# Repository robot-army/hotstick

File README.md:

# hotstick
An open-source hardware soldering station

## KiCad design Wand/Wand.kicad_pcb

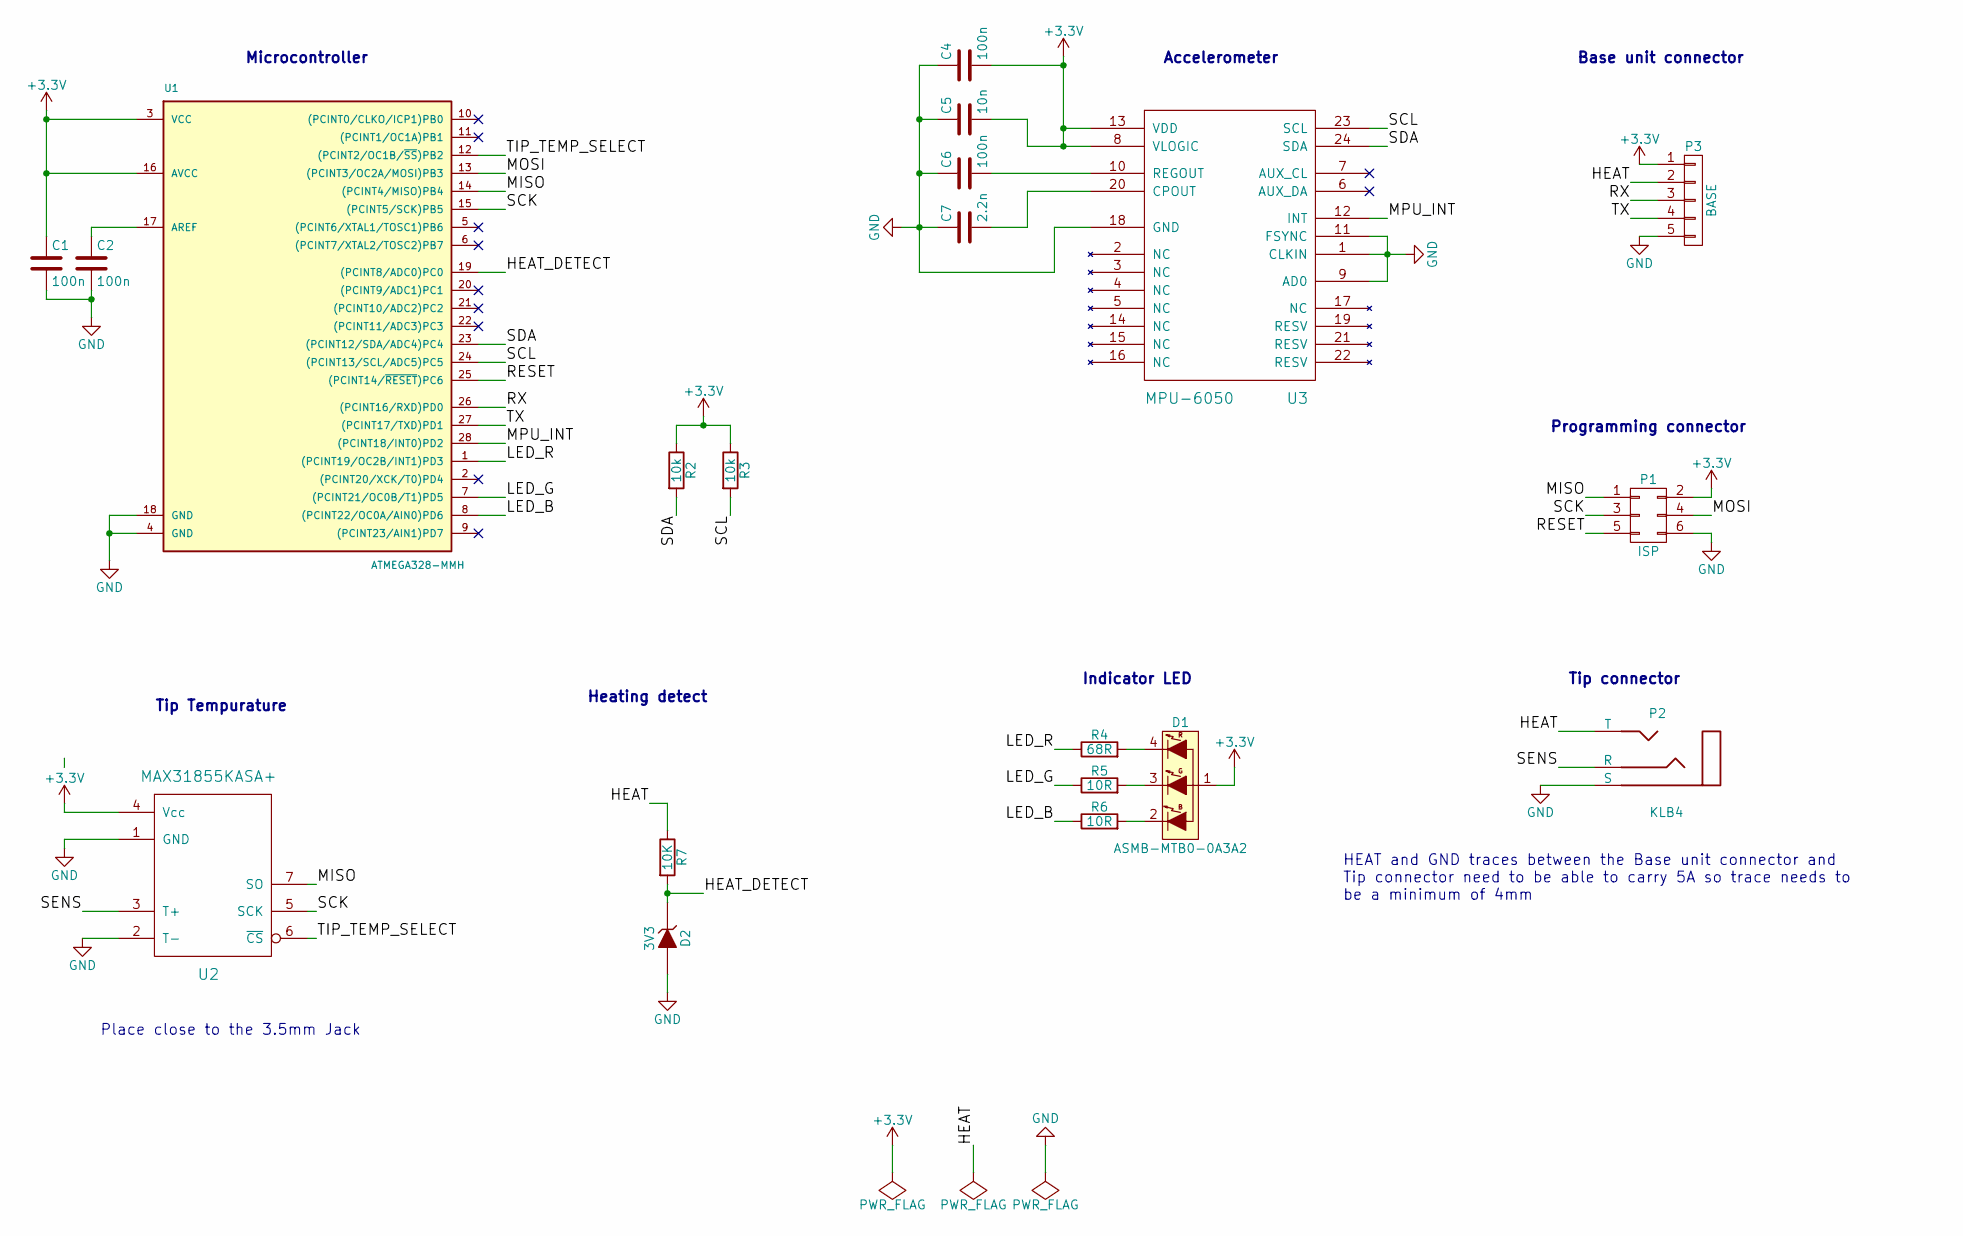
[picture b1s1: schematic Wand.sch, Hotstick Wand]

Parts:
C1, C2, C4, C6: 100n; C_0402
C5: 10n; C_0402
C7: 2.2n; C_0402
D1: ASMB-MTB0-0A3A2; Tri-Colour_LED
D2: 3V3; SOD-523
P1: ISP; ISP_pads_2x3
P2: KLB4; Jack_3.5mm_KLB
P3: BASE; Base_Connector
R2, R3: 10k; R_0402
R4: 68R; R_0402
R5, R6: 10R; R_0402
R7: 10K; R_0402
U1: ATMEGA328-MMH; QFN-28-1EP_4x4mm_Pitch0.45mm
U2: MAX31855KASA+; SOIC-8_3.9x4.9mm_Pitch1.27mm
U3: MPU-6050

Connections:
+3V3: C1.1, C4.2, C5.2, D1.1, P1.2, P3.1, R2.1, R3.1, U1.3 (VCC), U1.16 (AVCC), U2.4 (Vcc), U3.8 (VLOGIC), U3.13 (VDD)
/HEAT: P2.T, P3.2, R7.1
/HEAT_DETECT: D2.1 (K), R7.2, U1.19 ((PCINT8/ADC0)PC0)
/LED_B: R6.1, U1.8 ((PCINT22/OC0A/AIN0)PD6)
/LED_G: R5.1, U1.7 ((PCINT21/OC0B/T1)PD5)
/LED_R: R4.1, U1.1 ((PCINT19/OC2B/INT1)PD3)
/MISO: P1.1, U1.14 ((PCINT4/MISO)PB4), U2.7 (SO)
/MOSI: P1.4, U1.13 ((PCINT3/OC2A/MOSI)PB3)
/MPU_INT: U1.28 ((PCINT18/INT0)PD2), U3.12 (INT)
/RESET: P1.5, U1.25 ((PCINT14/~RESET~)PC6)
/RX: P3.3, U1.26 ((PCINT16/RXD)PD0)
/SCK: P1.3, U1.15 ((PCINT5/SCK)PB5), U2.5 (SCK)
/SCL: R3.2, U1.24 ((PCINT13/SCL/ADC5)PC5), U3.23 (SCL)
/SDA: R2.2, U1.23 ((PCINT12/SDA/ADC4)PC4), U3.24 (SDA)
/SENS: P2.R, U2.3 (T+)
/TIP_TEMP_SELECT: U1.12 ((PCINT2/OC1B/~SS~)PB2), U2.6 (~CS)
/TX: P3.4, U1.27 ((PCINT17/TXD)PD1)
GND: C1.2, C2.2, C4.1, C5.1, C6.1, C7.1, D2.2 (A), P1.6, P2.S, P3.5, U1.4 (GND), U1.18 (GND), U2.1 (GND), U2.2 (T-), U3.1 (CLKIN), U3.9 (AD0), U3.11 (FSYNC), U3.18 (GND)
unnamed: C2.1, U1.17 (AREF)
unnamed: C6.2, U3.10 (REGOUT)
unnamed: C7.2, U3.20 (CPOUT)
unnamed: D1.2 (B), R6.2
unnamed: D1.3 (G), R5.2
unnamed: D1.4 (R), R4.2

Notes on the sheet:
Tip connector
Programming connector
Base unit connector
Accelerometer
Microcontroller
Indicator LED
Place close to the 3.5mm Jack
Tip Tempurature
HEAT and GND traces between the Base unit connector and Tip connector need to be able to carry 5A so trace needs to be a minimum of 4mm
Heating detect

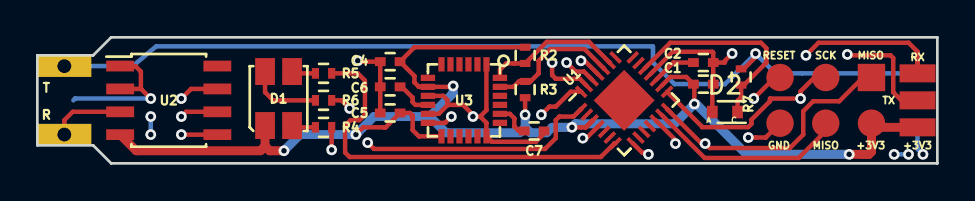
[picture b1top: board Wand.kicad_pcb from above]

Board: 4 copper layers, 50.0 x 7.0 mm, 20 parts (1 on the bottom side), 24 nets.

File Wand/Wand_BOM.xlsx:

Ref | Value | Footprint | Ordering code | Manufaturer | Supplier | Qty | Price (1+9) | Total (1+9) | Price (10+99) | Total (10+99) | Min V | Max V | URL
C2, C4, C6 | 100n | Capacitors_SMD:C_0402 |  |  |  | 3 |  | 0 |  | 0
C5 | 10n | Capacitors_SMD:C_0402 |  |  |  | 1 |  | 0 |  | 0
C7 | 2.2n | Capacitors_SMD:C_0402 |  |  |  | 1 |  | 0 |  | 0
D1 | ASMB-MTB0-0A3A2 | Wand:Tri-Colour_LED | 2401105 | AVAGO TECHNOLOGIES | Farnell | 1 | 0.1416 | 0.1416 | 0.13919999999999999 | 0.13919999999999999 |  |  | http://uk.farnell.com/avago-technologies/asmb-mtb0-0a3a2/led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
D2 | 3V3 Zener | Resistors_SMD:R_0402
P1 | ISP | Wand:ISP_pads_2x3 |  |  | N/A | 1 | 0 | 0 | 0 | 0
P2 | KLB4 | Wand:Jack_3.5mm_KLB | 1200144 | LUMBERG | Farnell | 1 | 1.1519999999999999 | 1.1519999999999999 | 1.0404 | 1.0404 |  |  | http://uk.farnell.com/lumberg/klb-4/connector-rca-jack-3-5mm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
P3 | BASE | Wand:Base_Connector |  |  | N/A | 1 | 0 | 0 | 0 | 0
R2, R3, R7 | 10K | Resistors_SMD:R_0402 |  |  |  | 3 |  | 0 |  | 0
R4 | 68R | Resistors_SMD:R_0402 |  |  |  | 1 |  | 0 |  | 0
R5, R6 | 10R | Resistors_SMD:R_0402 |  |  |  | 2 |  | 0 |  | 0
U1 | ATMEGA328-MMH | Wand:QFN-28-1EP_4x4mm_Pitch0.45mm | 2066293 | ATMEL | Farnell | 1 | 2.3639999999999999 | 2.3639999999999999 | 1.968 | 1.968 | 1.8 | 5.5 | http://uk.farnell.com/atmel/atmega328-mmh/mcu-8bit-atmega-20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
U2 | MAX31855KASA+ | Housings_SOIC:SOIC-8_3.9x4.9mm_Pitch1.27mm | 2515622 | MAXIM INTEGRATED PRODUCTS | Farnell | 1 | 4.2240000000000002 | 4.2240000000000002 | 3.84 | 3.84 | 3 | 3.6 | http://uk.farnell.com/maxim-integrated-products/max31855kasa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
U3 | MPU-6050 | Wand:MPU-6050 | 1864742 | INVENSENSE | Farnell | 1 | 8.6519999999999992 | 8.6519999999999992 | 5.9039999999999999 | 5.9039999999999999 | 2.375 | 3.46 | http://uk.farnell.com/invensense/mpu-6050/gyro-accel-6-axis-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
 |  |  |  |  |  |  |  | 16.5336 |  | 12.8916 | 3 | 3.46

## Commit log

2015-10-14 Added license
    Added CERN OHL 1.2 as the hardware license. Still an open issue on
    software and branding licenses.
2015-10-14 add waffle.io badge
2015-11-09 Initial schematic for a prototype soldering iron with accelerometer and micro controller in the handle of the iron
2015-11-14 Changed logic voltage to 3.3V as the MCP-6050 is 3,3v (as are most accelerometers)
2015-11-14 Use UART to communicate with the base unit, should be more reliable than I2C over long (1-2m).
2015-11-14 Added the support passive components for the MPU-6050.
2015-11-14 Corrected the ATMega 328 part number, needed the 28-pin VQFN package 4x4mm
2015-11-14 Picked an RGB LED part and selected the correct resistor values
2015-11-14 Datasheets for the components
2015-11-14 Fixed a 5v that should be 3.3v
2015-11-14 Updated with changes
2015-11-17 Added logic to detect the tip being inserted
2015-11-17 Added TMP100 temp sensor to measure the temp at the cold junction.
2015-11-18 General tidy-up and added a 100nF cap on AREF.
2015-11-18 Updated after changes
2015-11-20 Updated the Op-amp for the smaller OPA336N version
2016-01-03 Added a few footprints
2016-01-04 Corrected the schematic to use the 28pin version of the ATMEGA 328
2016-01-04 Added project specific footprint library
2016-01-04 Footprint for ATMega328-MM
2016-01-04 Added footprint for the LED
2016-01-11 Changed 3.5mm jack to an EBS35 style jack as a) I have some and b) some one had already done the footprint
2016-01-11 Set the footprint of the 3.5mm socket
2016-01-12 More 3.5mm Jack data sheets
2016-01-12 Another day, another 3.5mm Jack. This time just a basic panel mount one. The PCB mount ones are not going to fit in the required form factor.
2016-01-12 Removed the crystal and took a few changes to match the RFm69Pi module from Open Energy Monitor as that works with Serial and no crystal.
2016-01-13 Changed over to using the MAX31855 for reading the temperature to reduce the component count and also make virtually all the wand digital signals
2016-01-13 Updated the net
2016-01-13 Exact part number for the Tip temp sensor
2016-01-13 Updated PDF to match latest circuit.
2016-01-18 Corrected the MAX31855 chip select line, should be D10 (pin 12) not pin 10
2016-01-18 Test sketches for the LED and thermocouple
2016-01-19 Simple test for the Accelerometer
2016-01-20 Custom footprints for the base and 3.5mm Jack
2016-01-20 Updated net file
2016-01-20 Updated the PDF of the schematic
2016-01-20 Connected the MPU interrupt, needed by the http://www.i2cdevlib.com/ library for the MPU-6050
2016-01-20 Initial PCB layout, still work in progress.
2016-01-21 Sorted out the trace for the tip power and finalised the rest of the layout for review
2016-01-21 PDFs of first review version
2016-01-21 Slight tweak to allow more copper for tip power rail
2016-01-21 Another small tweak to tip Power rail
2016-01-21 Yet more tweaks to tip power
2016-01-23 Tidy up of the silk screen
2016-01-24 Added back silk screen info
2016-01-26 Some more tidy ups
2016-01-26 Final (hopefully) tweaks to the silk screens
2016-01-28 Removed the capacitor from the Temp sensor to allow it to be centred and initial modifications to allow monitoring of when the tip is being heated.
2016-01-29 Removed reset pull-up (should not be needed as internally pulled up) to make room for the heat detect logic and layed out the remaining components for the heat detect.
2016-01-29 Updated to match the checked in schematic/layout
2016-01-29 Its d BOM
2016-01-29 Added Gerber files for rev 1
2016-01-29 Pick and place files
2016-03-27 Changed 0402 to sod-523 for Zener
2016-03-27 Finished change for 0402, also generated fabrication data
2016-03-27 Added production data for dirtyPCBs order 2019353
